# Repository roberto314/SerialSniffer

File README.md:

# SerialSniffer
A Board to to observe serial communication between two units.

Version 1.0

This is a small PCB with a STM32F401 "blackpill" Board ontop. It can measure the Baudrate with a timer and then switch to listen mode and relay the packets via USB to the host computer.

There are two hardware serial ports on the STM32 and one USB for shell and output.

Firmware is ChibiOS Link: https://www.chibios.org), Version is trunk from ChibiStudio 20. Compilation is done with ChibiStudio 20 on Linux.

### Usage ###

* Connect a USB Cable to the "blackpill" Board,
* Start a terminal (i use picocom - "picocom /dev/ttyACM0")
* press "ENTER" a shell prompt should appear: Serial_Sniffer>
* enter "help" to get a list of all commands
* connect the Jumper J8 (marked "Timer") to one of the channels
* when communication occurs there should be a "Baud: abcd" outpt at the console
* enter the Baudrate with "sbr abcd" and switch on the listeners with "son 1"

There are some Jumpers on the board. J3 and J4 and the solder Jumper on the back JP2 and JP3 lets you connect to different Pins of the DB-9 connector for non-standard pinouts. The Jumper Pin5 is for Ground which is usually on Pin5.

### Used Software and OS ###

* Linux Mint (21.3 cinnamon) (Link: https://linuxmint.com/)
* Sublime Text 3 (Link: https://www.sublimetext.com/)
* Chibi Studio 20 (IDE for ChibiOS) (Link: https://www.chibios.org/dokuwiki/doku.php?id=chibios:products:chibistudio:start)

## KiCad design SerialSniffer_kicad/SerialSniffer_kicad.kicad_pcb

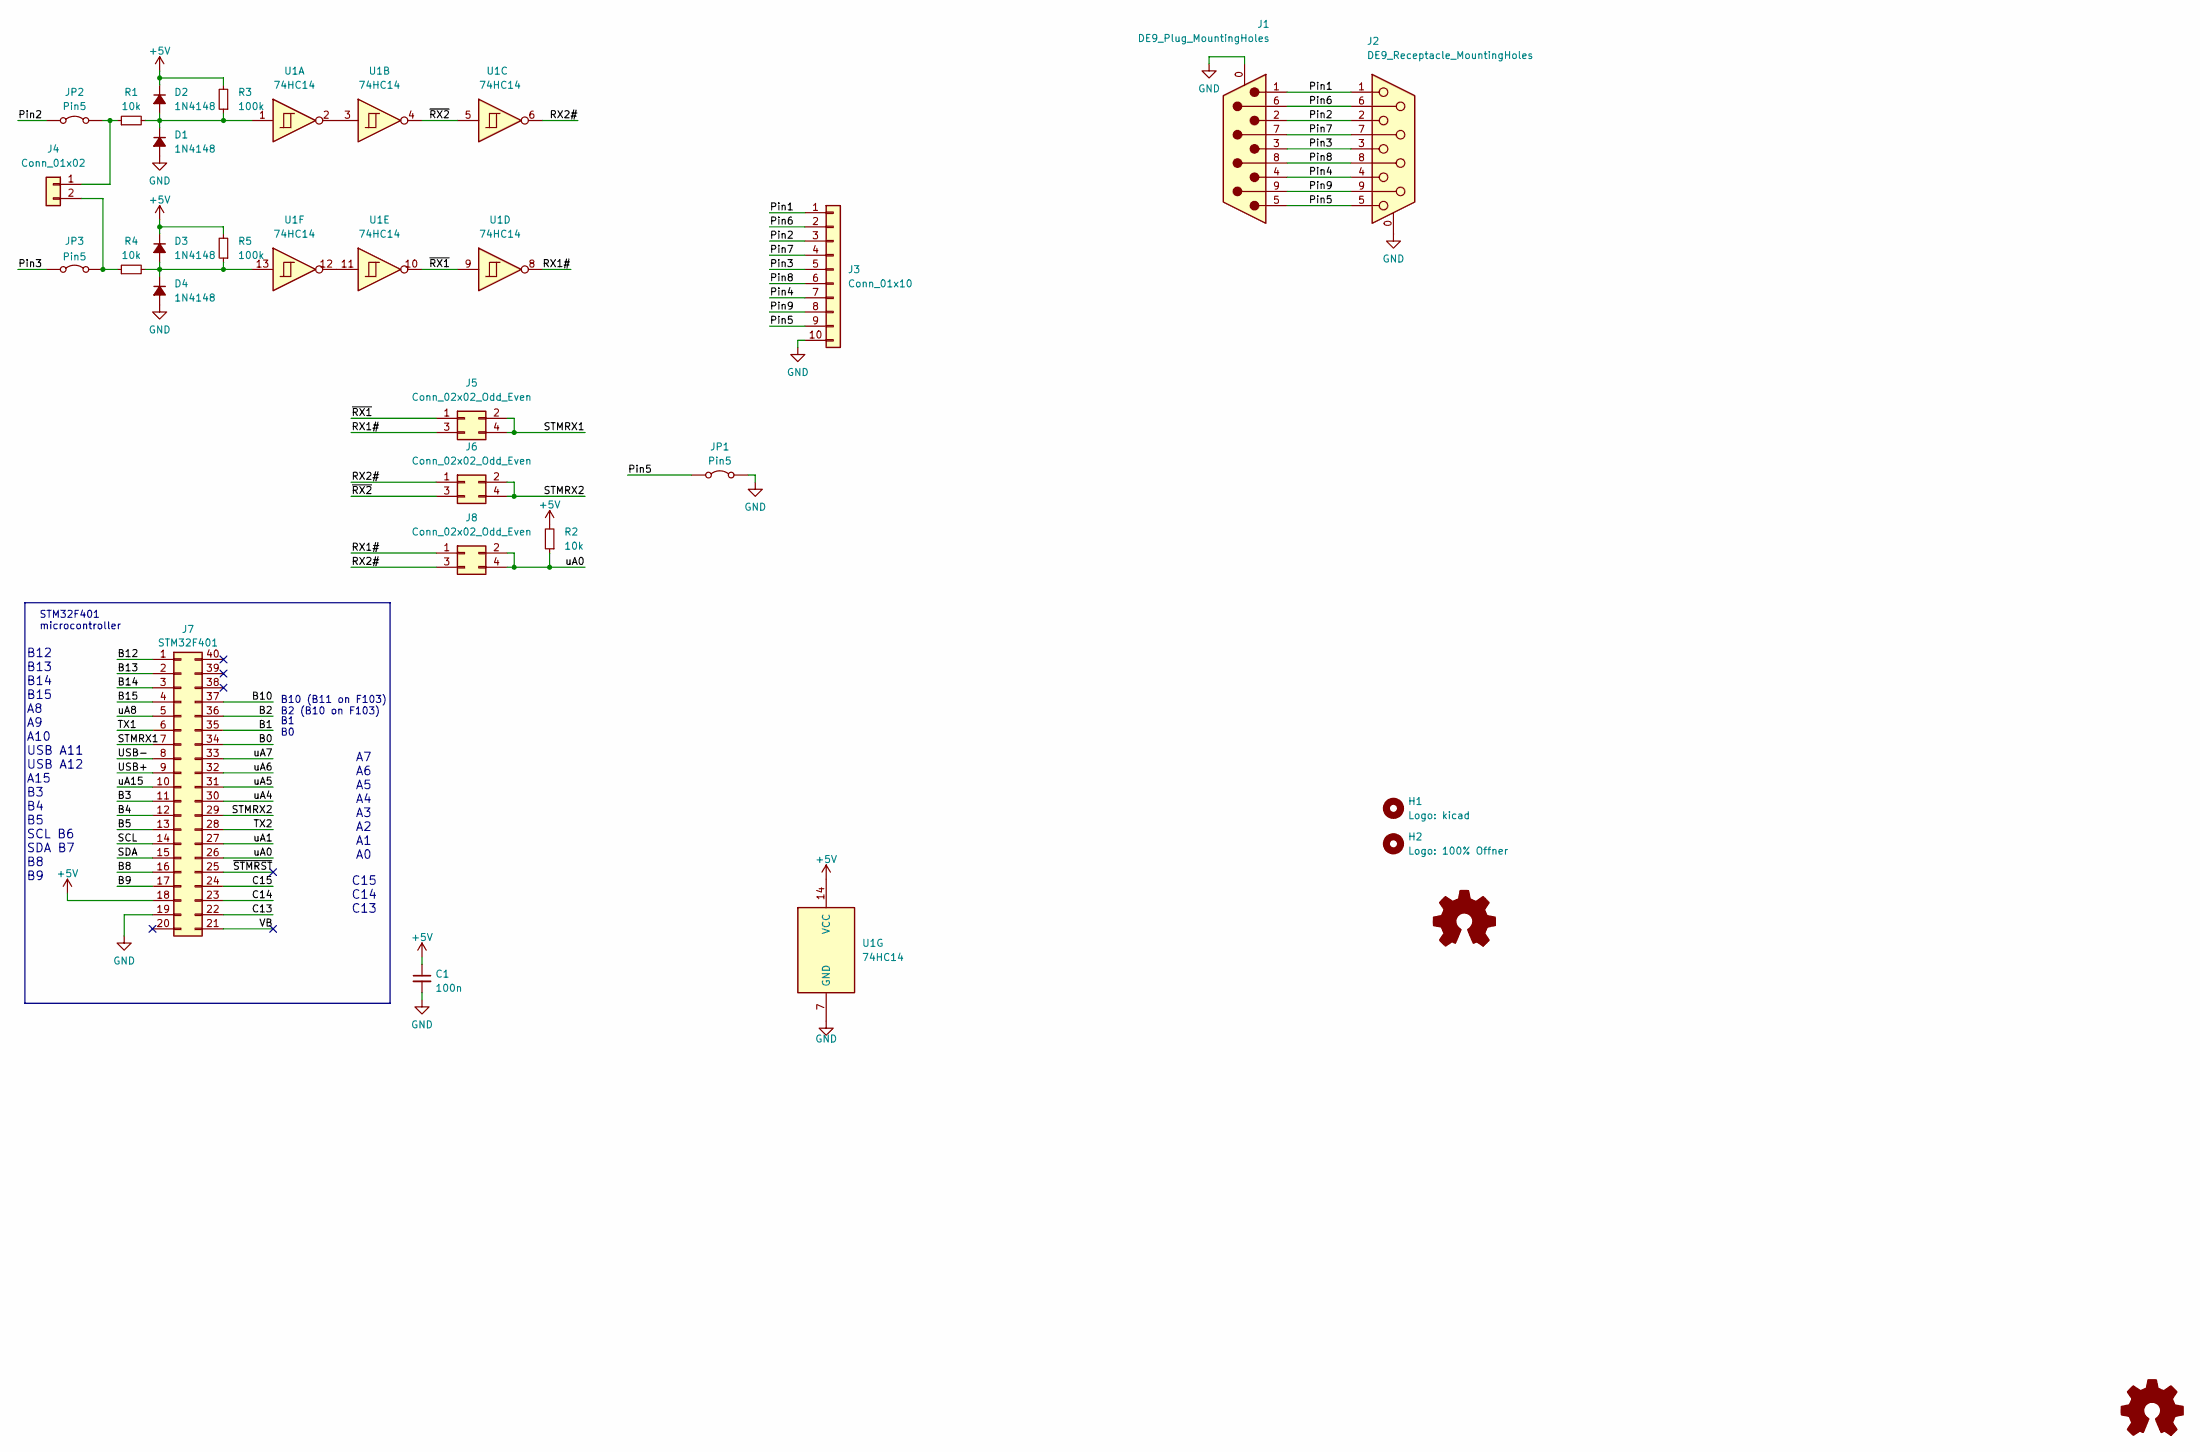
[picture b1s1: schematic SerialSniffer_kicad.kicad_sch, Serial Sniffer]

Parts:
C1: 100n; C_1206_3216Metric
D1, D2, D3, D4: 1N4148; D_1206_3216Metric_Pad1.42x1.75mm_HandSolder
H1: Logo: kicad; KiCad-Logo2_5mm_SilkScreen
H2: Logo: 100% Offner; Logo_100ProzentOffner_10x2.7mm
J1: DE9_Plug_MountingHoles; DSUB-9_Female_Horizontal_P2.77x2.84mm_EdgePinOffset7.70mm_H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
J2: DE9_Receptacle_MountingHoles; DSUB-9_Male_Horizontal_P2.77x2.84mm_EdgePinOffset7.70mm_Hou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
J3: Conn_01x10; PinSocket_1x10_P2.54mm_Vertical
J4: Conn_01x02; PinSocket_1x02_P2.54mm_Vertical
J5, J6, J8: Conn_02x02_Odd_Even; PinHeader_2x02_P2.54mm_Vertical
J7: STM32F401; DIP-40_W15.24mm_Socket_LongPads
JP1, JP2, JP3: Pin5; SolderJumper-2_P1.3mm_Bridged_RoundedPad1.0x1.5mm
R1, R2, R4: 10k; R_1206_3216Metric_Pad1.30x1.75mm_HandSolder
R3, R5: 100k; R_1206_3216Metric_Pad1.30x1.75mm_HandSolder
U1: 74HC14; DIP-14_W7.62mm_LongPads

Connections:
+5V: C1.1, D2.1 (K), D3.1 (K), J7.18, R2.2, R3.2, R5.2, U1.14 (VCC)
/B0: J7.34
/B1: J7.35
/B2: J7.36
/B3: J7.11
/B4: J7.12
/B5: J7.13
/B8: J7.16
/B9: J7.17
/B10: J7.37
/B12: J7.1
/B13: J7.2
/B14: J7.3
/B15: J7.4
/C13: J7.22
/C14: J7.23
/C15: J7.24
/Pin1: J1.1, J2.1, J3.1
/Pin2: J1.2, J2.2, J3.3, JP2.2 (B)
/Pin3: J1.3, J2.3, J3.5, JP3.2 (B)
/Pin4: J1.4, J2.4, J3.7
/Pin5: J1.5, J2.5, J3.9, JP1.1 (A)
/Pin6: J1.6, J2.6, J3.2
/Pin7: J1.7, J2.7, J3.4
/Pin8: J1.8, J2.8, J3.6
/Pin9: J1.9, J2.9, J3.8
/RX1#: J5.3, J8.1, U1.8
/RX2#: J6.1, J8.3, U1.6
/SCL: J7.14
/SDA: J7.15
/STMRX1: J5.2, J5.4, J7.7
/STMRX2: J6.2, J6.4, J7.29
/TX1: J7.6
/TX2: J7.28
/USB+: J7.9
/USB-: J7.8
/VB: J7.21
/uA0: J7.26, J8.2, J8.4, R2.1
/uA1: J7.27
/uA4: J7.30
/uA5: J7.31
/uA6: J7.32
/uA7: J7.33
/uA8: J7.5
/uA15: J7.10
/~RX1: J5.1, U1.9, U1.10
/~RX2: J6.3, U1.4, U1.5
/~STMRST: J7.25
GND: C1.2, D1.2 (A), D4.2 (A), J1.0 (PAD), J2.0 (PAD), J3.10, J7.19, JP1.2 (B), U1.7 (GND)
unnamed: D1.1 (K), D2.2 (A), R1.2, R3.1, U1.1
unnamed: D3.2 (A), D4.1 (K), R4.2, R5.1, U1.13
unnamed: J4.1, JP2.1 (A), R1.1
unnamed: J4.2, JP3.1 (A), R4.1
unnamed: U1.2, U1.3
unnamed: U1.11, U1.12

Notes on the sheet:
B1 B0
B10 (B11 on F103) B2 (B10 on F103)
A7 A6 A5 A4 A3 A2 A1 A0
B12 B13 B14 B15 A8 A9 A10 USB A11 USB A12 A15 B3 B4 B5 SCL B6 SDA B7 B8 B9
C15 C14 C13
STM32F401 microcontroller

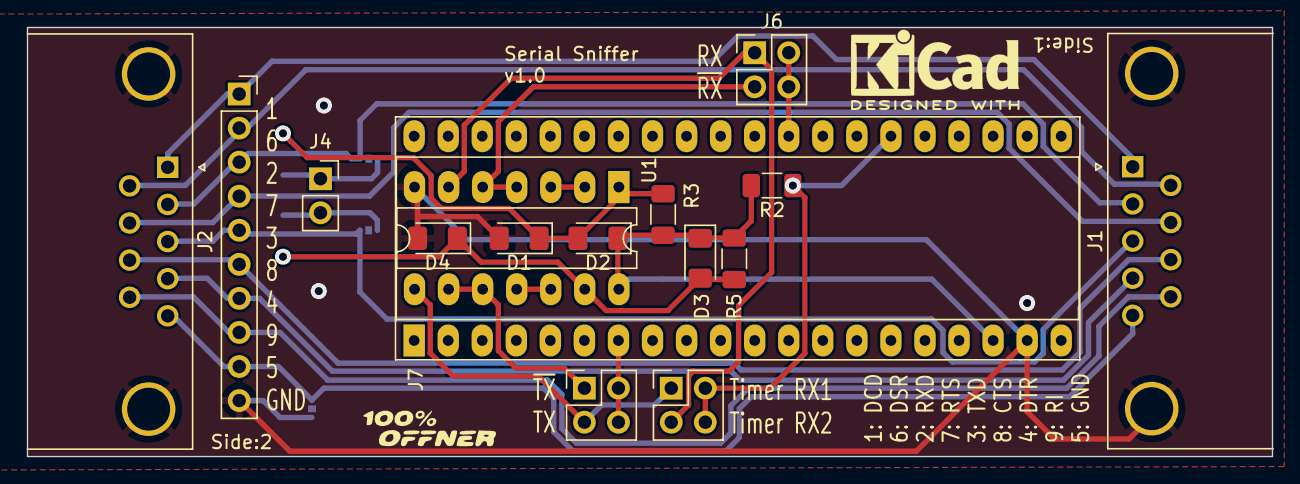
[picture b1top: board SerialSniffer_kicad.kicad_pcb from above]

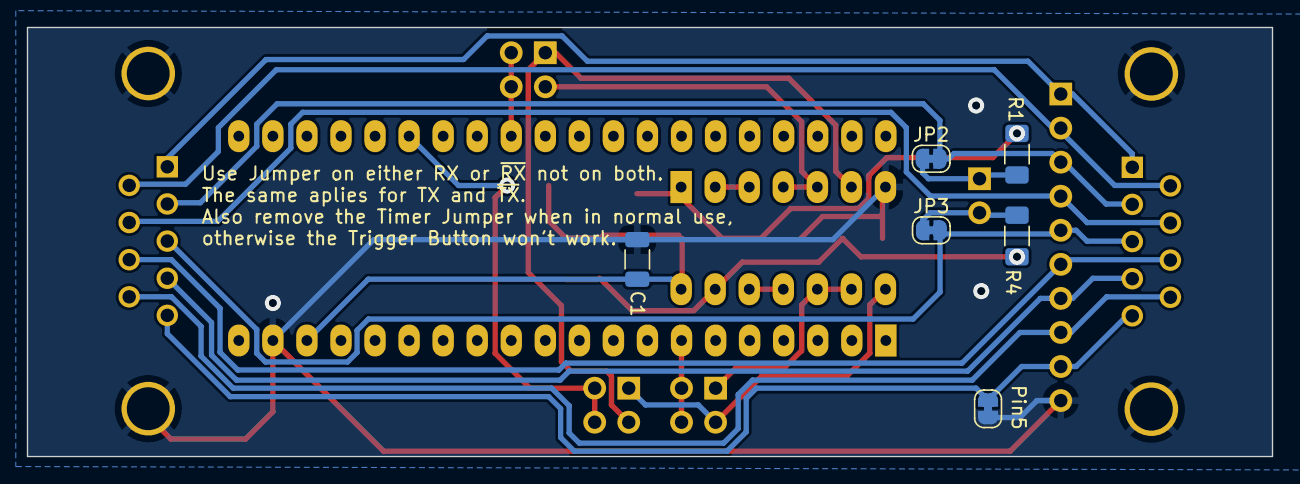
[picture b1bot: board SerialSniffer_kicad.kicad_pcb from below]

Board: 2 copper layers, 92.9 x 32.0 mm, 24 parts (6 on the bottom side), 24 nets.

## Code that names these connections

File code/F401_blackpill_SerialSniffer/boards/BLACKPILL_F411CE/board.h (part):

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 * GPIOB setup:
 *
 * PB0  - ARD_A3 ADC1_IN8           (input pullup).
 * PB1  - PIN1                      (input pullup).
 * PB2  - PIN2                      (input pullup).
 * PB3  - SWO ARD_D3                (alternate 0).
 * PB4  - ARD_D5                    (input floating).
 * PB5  - ARD_D4                    (input pullup).
 * PB6  - ARD_D10                   (input pullup).
 * PB7  - PIN7                      (input pullup).
 * PB8  - ARD_D15                   (input pullup).
 * PB9  - ARD_D14                   (input pullup).
 * PB10 - ARD_D6                    (input pullup).
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 *
 * PC0  - ARD_A5 ADC1_IN10          (input pullup).
 * PC1  - ARD_A4 ADC1_IN11          (input pullup).
 * PC2  - PIN2                      (input pullup).
 * PC3  - PIN3                      (input pullup).
 * PC4  - PIN4                      (input pullup).
 * PC5  - PIN5                      (input pullup).
 * PC6  - PIN6                      (input pullup).
 * PC7  - ARD_D9                    (input pullup).
 * PC8  - PIN8                      (input pullup).
 * PC9  - PIN9                      (input pullup).
 * PC10 - PIN10                     (input pullup).
 * PC11 - PIN11                     (input pullup).
 * PC12 - PIN12                     (input pullup).
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 * GPIOD setup:
 *
 * PD0  - PIN0                      (input pullup).
 * PD1  - PIN1                      (input pullup).
 * PD2  - PIN2                      (input pullup).
 * PD3  - PIN3                      (input pullup).
 * PD4  - PIN4                      (input pullup).
 * PD5  - PIN5                      (input pullup).
 * PD6  - PIN6                      (input pullup).
 * PD7  - PIN7                      (input pullup).
 * PD8  - PIN8                      (input pullup).
 * PD9  - PIN9                      (input pullup).
 * PD10 - PIN10                     (input pullup).
 * PD11 - PIN11                     (input pullup).
 * PD12 - PIN12                     (input pullup).
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 * GPIOE setup:
 *
 * PE0  - PIN0                      (input pullup).
 * PE1  - PIN1                      (input pullup).
 * PE2  - PIN2                      (input pullup).
 * PE3  - PIN3                      (input pullup).
 * PE4  - PIN4                      (input pullup).
 * PE5  - PIN5                      (input pullup).
 * PE6  - PIN6                      (input pullup).
 * PE7  - PIN7                      (input pullup).
 * PE8  - PIN8                      (input pullup).
 * PE9  - PIN9                      (input pullup).
 * PE10 - PIN10                     (input pullup).
 * PE11 - PIN11                     (input pullup).
 * PE12 - PIN12                     (input pullup).
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 * GPIOF setup:
 *
 * PF0  - PIN0                      (input pullup).
 * PF1  - PIN1                      (input pullup).
 * PF2  - PIN2                      (input pullup).
 * PF3  - PIN3                      (input pullup).
 * PF4  - PIN4                      (input pullup).
 * PF5  - PIN5                      (input pullup).
 * PF6  - PIN6                      (input pullup).
 * PF7  - PIN7                      (input pullup).
 * PF8  - PIN8                      (input pullup).
 * PF9  - PIN9                      (input pullup).
 * PF10 - PIN10                     (input pullup).
 * PF11 - PIN11                     (input pullup).
 * PF12 - PIN12                     (input pullup).
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 * GPIOG setup:
 *
 * PG0  - PIN0                      (input pullup).
 * PG1  - PIN1                      (input pullup).
 * PG2  - PIN2                      (input pullup).
 * PG3  - PIN3                      (input pullup).
 * PG4  - PIN4                      (input pullup).
 * PG5  - PIN5                      (input pullup).
 * PG6  - PIN6                      (input pullup).
 * PG7  - PIN7                      (input pullup).
 * PG8  - PIN8                      (input pullup).
 * PG9  - PIN9                      (input pullup).
 * PG10 - PIN10                     (input pullup).
 * PG11 - PIN11                     (input pullup).
 * PG12 - PIN12                     (input pullup).
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 *
 * PH0  - OSC_IN                    (input floating).
 * PH1  - OSC_OUT                   (input floating).
 * PH2  - PIN2                      (input pullup).
 * PH3  - PIN3                      (input pullup).
 * PH4  - PIN4                      (input pullup).
 * PH5  - PIN5                      (input pullup).
 * PH6  - PIN6                      (input pullup).
 * PH7  - PIN7                      (input pullup).
 * PH8  - PIN8                      (input pullup).
 * PH9  - PIN9                      (input pullup).
 * PH10 - PIN10                     (input pullup).
 * PH11 - PIN11                     (input pullup).
 * PH12 - PIN12                     (input pullup).
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 * GPIOI setup:
 *
 * PI0  - PIN0                      (input pullup).
 * PI1  - PIN1                      (input pullup).
 * PI2  - PIN2                      (input pullup).
 * PI3  - PIN3                      (input pullup).
 * PI4  - PIN4                      (input pullup).
 * PI5  - PIN5                      (input pullup).
 * PI6  - PIN6                      (input pullup).
 * PI7  - PIN7                      (input pullup).
 * PI8  - PIN8                      (input pullup).
 * PI9  - PIN9                      (input pullup).
 * PI10 - PIN10                     (input pullup).
 * PI11 - PIN11                     (input pullup).
 * PI12 - PIN12                     (input pullup).
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
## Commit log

2024-10-17 Initial
2024-10-17 Formatting different
2024-11-14 new code
2024-11-14 output formatting changes
2025-05-02 new code, bugfixed, should work

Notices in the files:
code/F401_blackpill_SerialSniffer/boards/BLACKPILL_F411CE/board.h:
ChibiOS - Copyright (C) 2006..2020 Giovanni Di Sirio
Licensed under the Apache License, Version 2.0 (the "License");
